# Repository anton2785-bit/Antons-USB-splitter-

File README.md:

# Antons-USB-splitter-
---
## What is this project

* This is a small PCB that can take 1 input signal via USB A and output 4 separate USB A signals.  
---
## Why i made this project

* I made the USB splitter because I want to have a USB hub closer to my keyboard or me in general so that I dont have to dive behind my  PC to plug a USB.

  ---
  ## Images
  * This is an image of the schematic:

  * This is the PCB:

  * The 3D model of the PCB:

  ---
  
  ## Assembly
  * First you need to soulder all of the capacitors (I think 5), the fuses ( 5 of them) and the crystal.
  * Then you can soulder the bigger components like the chip and the USB ports.
  * Thats it.
 ## BOM
 
| Component | Purpose | Qty | Cost (USD) | Distributor |
|-----------|---------|-----|------------|-------------|
| Capacitors 100nF | Decoupling | 1 lot | $1.90 | [AliExpress](https://www.aliexpress.com/item/1005007470747384.html) |
| Crystal 12MHz | Clock source | 1 lot | $1.80 | [AliExpress](https://www.aliexpress.com/item/1005006126635124.html) |
| USB Connectors | Signal in/out | 1 lot | $4.08 | [AliExpress](https://www.aliexpress.com/item/1005006092828018.html) |
| Polyfuses | Overcurrent protection | 1 lot | $4.01 | [AliExpress](https://www.aliexpress.com/item/32918666236.html) |
| Capacitors many values | Decoupling | 1 lot | $4.31 | [AliExpress](https://www.aliexpress.com/item/1005006157020955.html) |
| PCB | Board fabrication | 1 | $4.20 | JLCPCB |
| **Total** | | | **$20.30** | |
---
## Credits

* Designed and built by *(Anton/ Anton-2785-bit)
* Inspired by open‑source mechanical keyboard and hackpad communities (https://macondo.hackclub.com/).

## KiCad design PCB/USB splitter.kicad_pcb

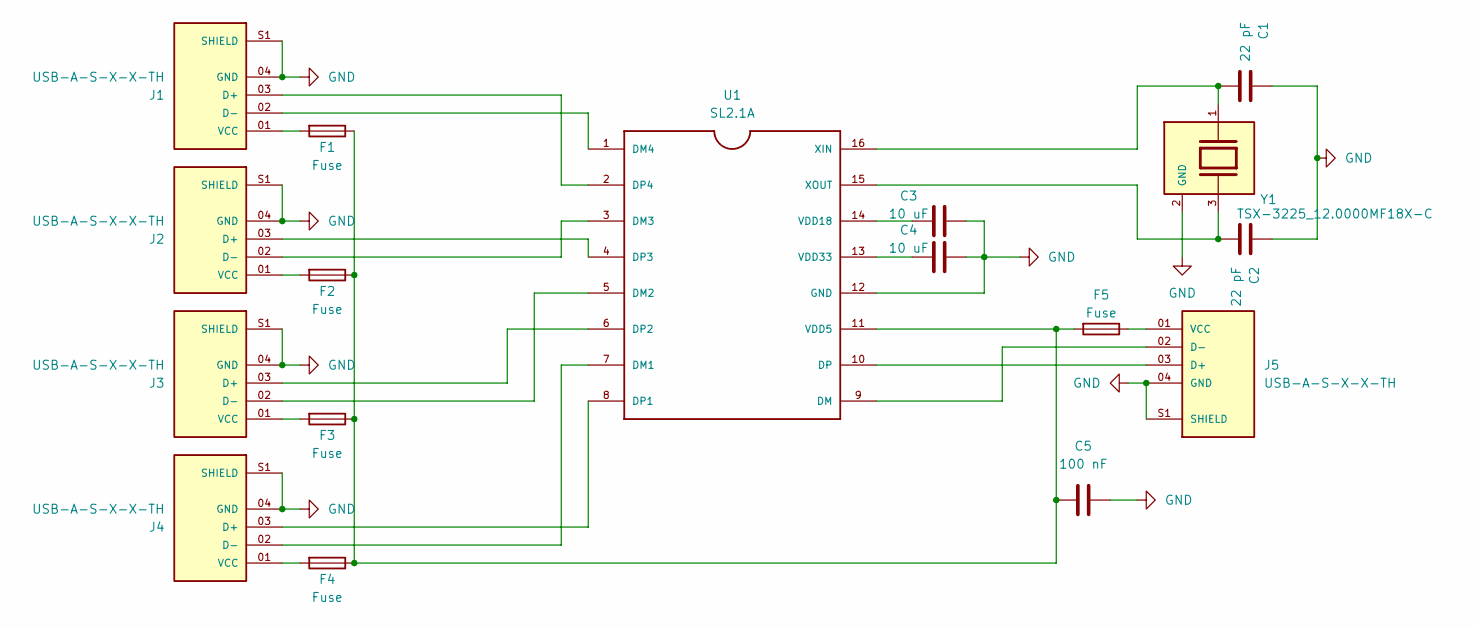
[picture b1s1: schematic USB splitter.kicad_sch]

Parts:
C1, C2: 22 pF; C_0805_2012Metric_Pad1.18x1.45mm_HandSolder
C3, C4: 10 uF; C_0805_2012Metric_Pad1.18x1.45mm_HandSolder
C5: 100 nF; C_0805_2012Metric_Pad1.18x1.45mm_HandSolder
F1, F2, F3, F4, F5: Fuse; Fuse_0805_2012Metric_Pad1.15x1.40mm_HandSolder
J1, J2, J3, J4, J5: USB-A-S-X-X-TH; SAMTEC_USB-A-S-X-X-TH; PARTREV R
U1: SL2.1A; SO16
Y1: TSX-3225_12.0000MF18X-C; Crystal_SMD_SeikoEpson_TSX3225-4Pin_3.2x2.5mm_HandSoldering; PARTREV N/A

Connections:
GND: C1.1, C2.1, C3.2, C4.2, C5.2, J1.04 (GND), J1.S1 (SHIELD), J1.S2 (SHIELD), J2.04 (GND), J2.S1 (SHIELD), J2.S2 (SHIELD), J3.04 (GND), J3.S1 (SHIELD), J3.S2 (SHIELD), J4.04 (GND), J4.S1 (SHIELD), J4.S2 (SHIELD), J5.04 (GND), J5.S1 (SHIELD), J5.S2 (SHIELD), U1.12 (GND), Y1.2 (GND), Y1.4 (GND)
unnamed: J1.03 (D+), U1.2 (DP4)
unnamed: J1.02 (D-), U1.1 (DM4)
unnamed: F1.2, J1.01 (VCC)
unnamed: J2.03 (D+), U1.4 (DP3)
unnamed: J2.02 (D-), U1.3 (DM3)
unnamed: F2.2, J2.01 (VCC)
unnamed: J3.03 (D+), U1.6 (DP2)
unnamed: J3.02 (D-), U1.5 (DM2)
unnamed: F3.2, J3.01 (VCC)
unnamed: J4.03 (D+), U1.8 (DP1)
unnamed: J4.02 (D-), U1.7 (DM1)
unnamed: F4.2, J4.01 (VCC)
unnamed: J5.03 (D+), U1.10 (DP)
unnamed: J5.02 (D-), U1.9 (DM)
unnamed: F5.1, J5.01 (VCC)
unnamed: C5.1, F1.1, F2.1, F3.1, F4.1, F5.2, U1.11 (VDD5)
unnamed: C3.1, U1.14 (VDD18)
unnamed: C4.1, U1.13 (VDD33)
unnamed: C1.2, U1.16 (XIN), Y1.1
unnamed: C2.2, U1.15 (XOUT), Y1.3

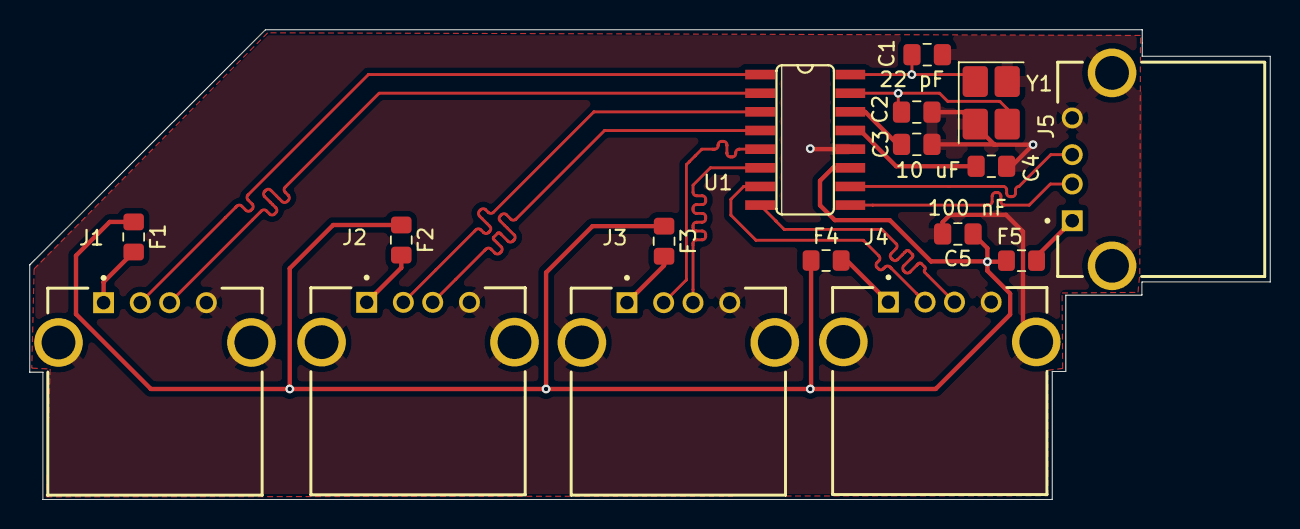
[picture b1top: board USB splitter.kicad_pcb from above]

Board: 2 copper layers, 84.5 x 32.0 mm, 17 parts (0 on the bottom side), 21 nets.

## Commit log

2026-05-02 File update
